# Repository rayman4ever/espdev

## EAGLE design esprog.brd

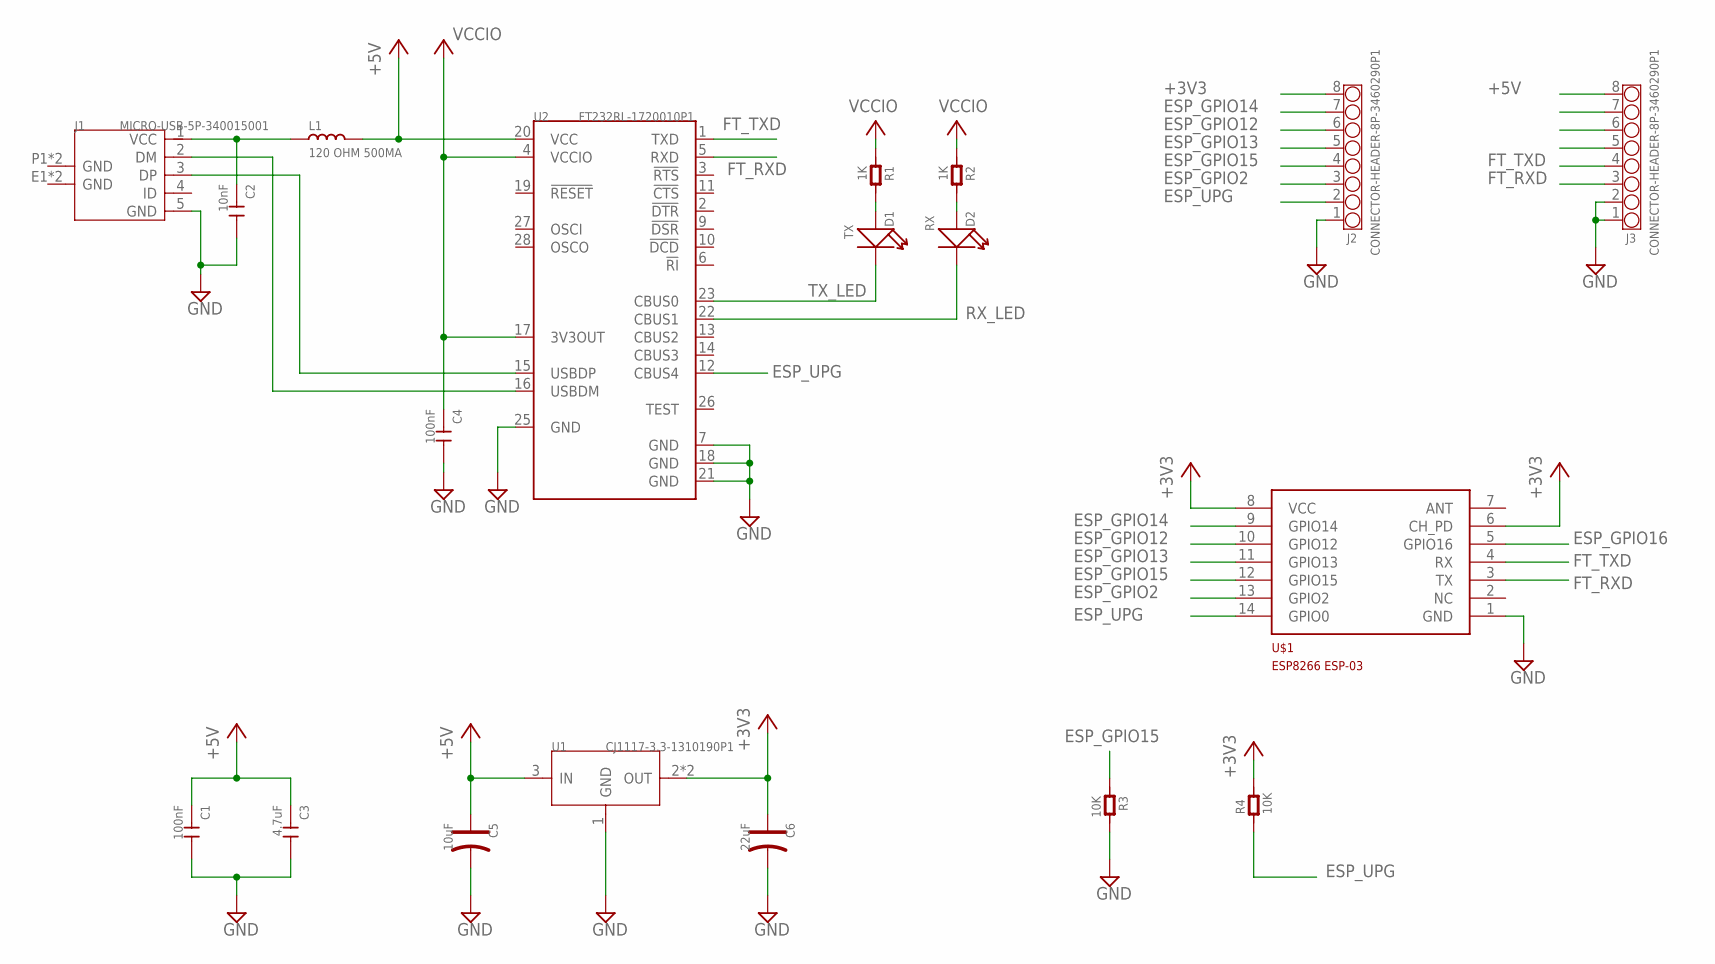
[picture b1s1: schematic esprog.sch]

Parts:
C1, C4: 100nF; C0603
C2: 10nF; C0603
C3: 4.7uF; C0805
C5: 10uF; AVX-B
C6: 22uF; AVX-B
D1: TX; LED-0603
D2: RX; LED-0603
J1: MICRO-USB-5P-340015001; B-SMD-5P
J2, J3: CONNECTOR-HEADER-8P-3460290P1; 1X8P-2.54-8.5-BLACK-FEMALE
L1: 120 OHM 500MA; L0805
R1, R2: 1K; R0805
R3, R4: 10K; R0805
U1: CJ1117-3.3-1310190P1; SOT223
U2: FT232RL-1720010P1; SSOP28
U$1: ESP8266_ESP-03; ESP-03

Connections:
+3V3: C6.+, J2.8, R4.2, U1.2 (OUT), U1.TER (OUT), U$1.6 (CH_PD), U$1.8 (VCC)
+5V: C1.1, C3.1, C5.+, J3.8, L1.2, U1.3 (IN), U2.20 (VCC)
DM: J1.2 (DM), U2.16 (USBDM)
DP: J1.3 (DP), U2.15 (USBDP)
ESP_GPIO2: J2.3, U$1.13 (GPIO2)
ESP_GPIO12: J2.6, U$1.10 (GPIO12)
ESP_GPIO13: J2.5, U$1.11 (GPIO13)
ESP_GPIO14: J2.7, U$1.9 (GPIO14)
ESP_GPIO15: J2.4, R3.1, U$1.12 (GPIO15)
ESP_GPIO16: U$1.5 (GPIO16)
ESP_UPG: J2.2, R4.1, U2.12 (CBUS4), U$1.14 (GPIO0)
FT_RXD: J3.3, U2.5 (RXD), U$1.3 (TX)
FT_TXD: J3.4, U2.1 (TXD), U$1.4 (RX)
GND: C1.2, C2.2, C3.2, C4.2, C5.-, C6.-, J1.5 (GND), J2.1, J3.1, J3.2, R3.2, U1.1 (GND), U2.7 (GND), U2.18 (GND), U2.21 (GND), U2.25 (GND), U$1.1 (GND)
unnamed: D1.+, R1.2
unnamed: D2.+, R2.2
RX_LED: D2.-, U2.22 (CBUS1)
TX_LED: D1.-, U2.23 (CBUS0)
VCCIO: C4.1, R1.1, R2.1, U2.4 (VCCIO), U2.17 (3V3OUT)
VUSB: C2.1, J1.1 (VCC), L1.1

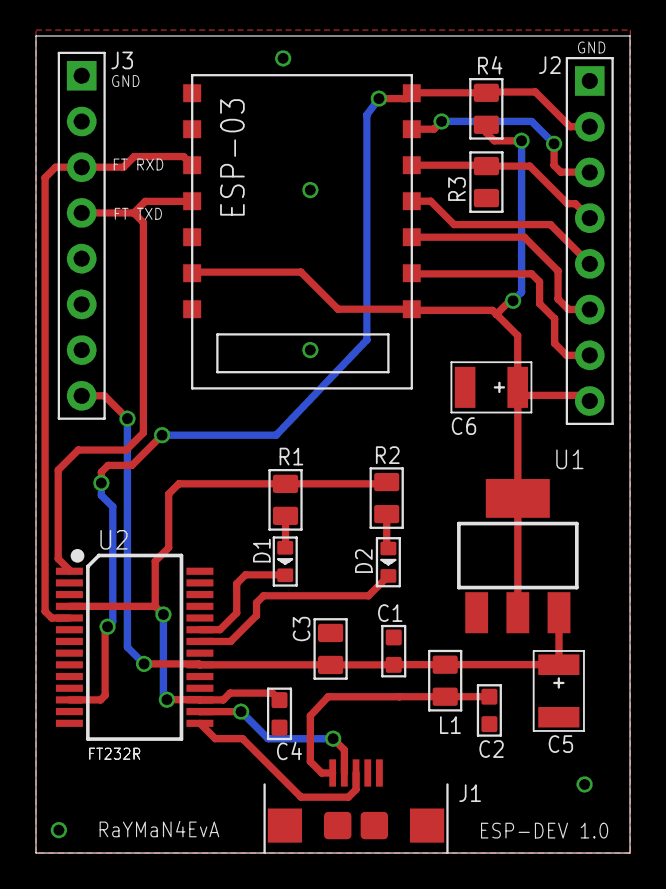
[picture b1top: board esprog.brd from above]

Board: 2 copper layers, 33.0 x 45.4 mm, 19 parts (0 on the bottom side), 19 nets.

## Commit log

2014-12-31 initial schematic
2015-01-03 Final v1.0 PCB - Added PCB Design - Finished Circuit Schematic
2015-01-10 Updated board file
